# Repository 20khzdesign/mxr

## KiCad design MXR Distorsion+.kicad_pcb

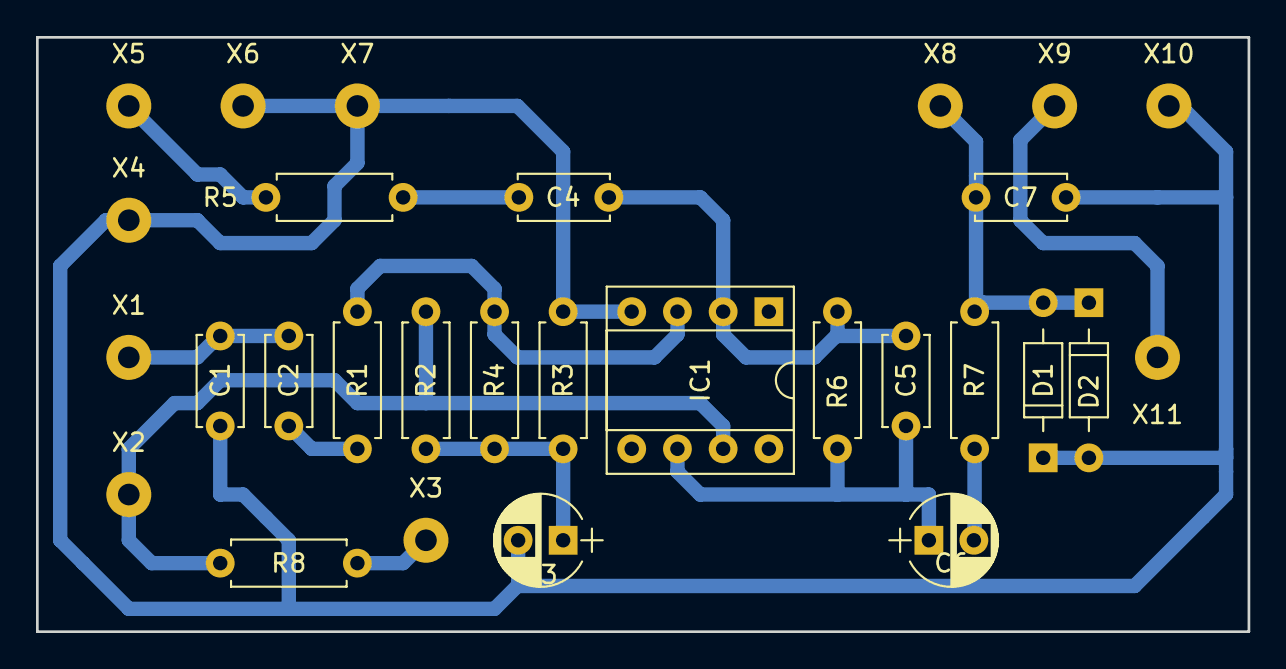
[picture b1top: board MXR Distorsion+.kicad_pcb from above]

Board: 2 copper layers, 67.3 x 33.0 mm, 29 parts (0 on the bottom side), 14 nets.

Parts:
C1, C7: 1n; C1
C2: 10n; C1
C3, C6: 1u; CP1
C4: 47nC; C1
C5: 10p; C1
D1, D2: D
IC1: LM741; DIP_8
R1, R7: 10k; R
R2, R3, R4, R6: 1M; R
R5: 4k7; R
R8: 2k2; R
X1: in; Pad_2,5
X2: +9V; Pad_2,5
X3: led; Pad_2,5
X4: GND; Pad_2,5
X5: Pa; Pad_2,5
X6: Pb; Pad_2,5
X7: Pc; Pad_2,5
X8: Pd; Pad_2,5
X9: Pe; Pad_2,5
X10: Pf; Pad_2,5
X11: out; Pad_2,5

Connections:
GND: C1.1, C3.2, C7.1, D1.1, D2.2, IC1.4, R3.2, X4.1, X6.1, X7.1, X10.1
unnamed: IC1.7, R2.1, R8.1, X2.1
unnamed: C1.2, C2.2, X1.1
unnamed: C2.1, R1.1
unnamed: C3.1, R2.2, R3.1, R4.1
unnamed: C4.1, C5.2, IC1.2, R6.2
unnamed: C4.2, R5.2
unnamed: C5.1, C6.1, IC1.6, R6.1
unnamed: C6.2, R7.2
unnamed: C7.2, D1.2, D2.1, R7.1, X8.1
unnamed: R8.2, X3.1
unnamed: IC1.3, R1.2, R4.2
unnamed: X9.1, X11.1
unnamed: R5.1, X5.1

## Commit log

2017-09-08 commit inicial
